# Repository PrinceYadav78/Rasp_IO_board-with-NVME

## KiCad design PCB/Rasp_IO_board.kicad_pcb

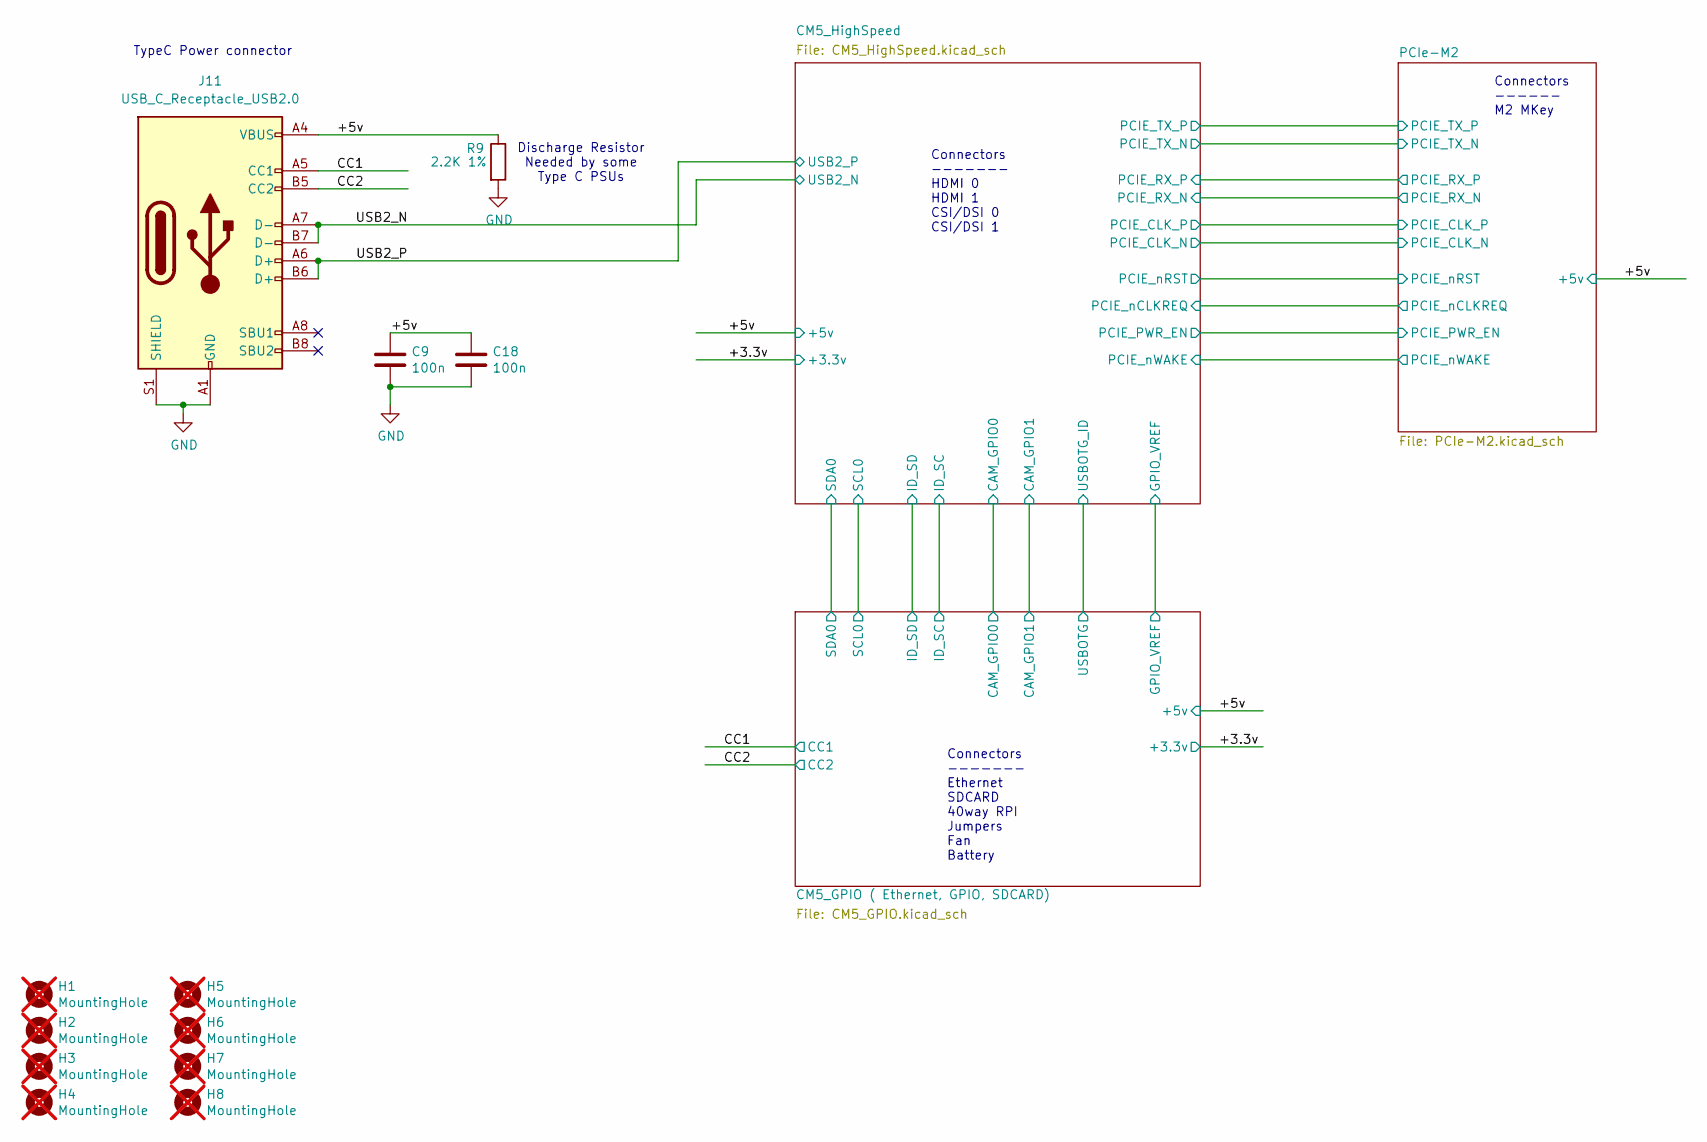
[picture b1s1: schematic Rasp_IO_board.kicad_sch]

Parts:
C9, C18: 100n; C_0402_1005Metric; Part Description 0.1uF 10% 16V Ceramic Capacitor X7R 040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
H1, H2, H3, H4, H5, H6, H7, H8: MountingHole; MountingHole_2.7mm_M2.5_DIN965; Part Description M2.5 mounting hole; not fitted
J11: USB_C_Receptacle_USB2.0; USB_C_Receptacle_GCT_USB4105-xx-A_16P_TopMnt_Horizontal; Part Description USBC USB2 data and power connector
R9: 2.2K 1%; R_0402_1005Metric; Part Description Resistor 2.2K M1005 1% 63mW

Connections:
/+5v: C9.1, C18.1, J11.A4 (VBUS), J11.A9 (VBUS), J11.B4 (VBUS), J11.B9 (VBUS), R9.1; also elsewhere on the board
/CC1: J11.A5 (CC1); also elsewhere on the board
/CC2: J11.B5 (CC2); also elsewhere on the board
/USB2_N: J11.A7 (D-), J11.B7 (D-); also elsewhere on the board
/USB2_P: J11.A6 (D+), J11.B6 (D+); also elsewhere on the board
GND: C9.2, C18.2, J11.A1 (GND), J11.A12 (GND), J11.B1 (GND), J11.B12 (GND), J11.S1 (SHIELD), R9.2; also elsewhere on the board

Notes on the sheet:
Connectors ------- Ethernet SDCARD 40way RPI Jumpers Fan Battery
Connectors ------ M2 MKey
Discharge Resistor Needed by some Type C PSUs
TypeC Power connector
Connectors ------- HDMI 0 HDMI 1 CSI/DSI 0 CSI/DSI 1

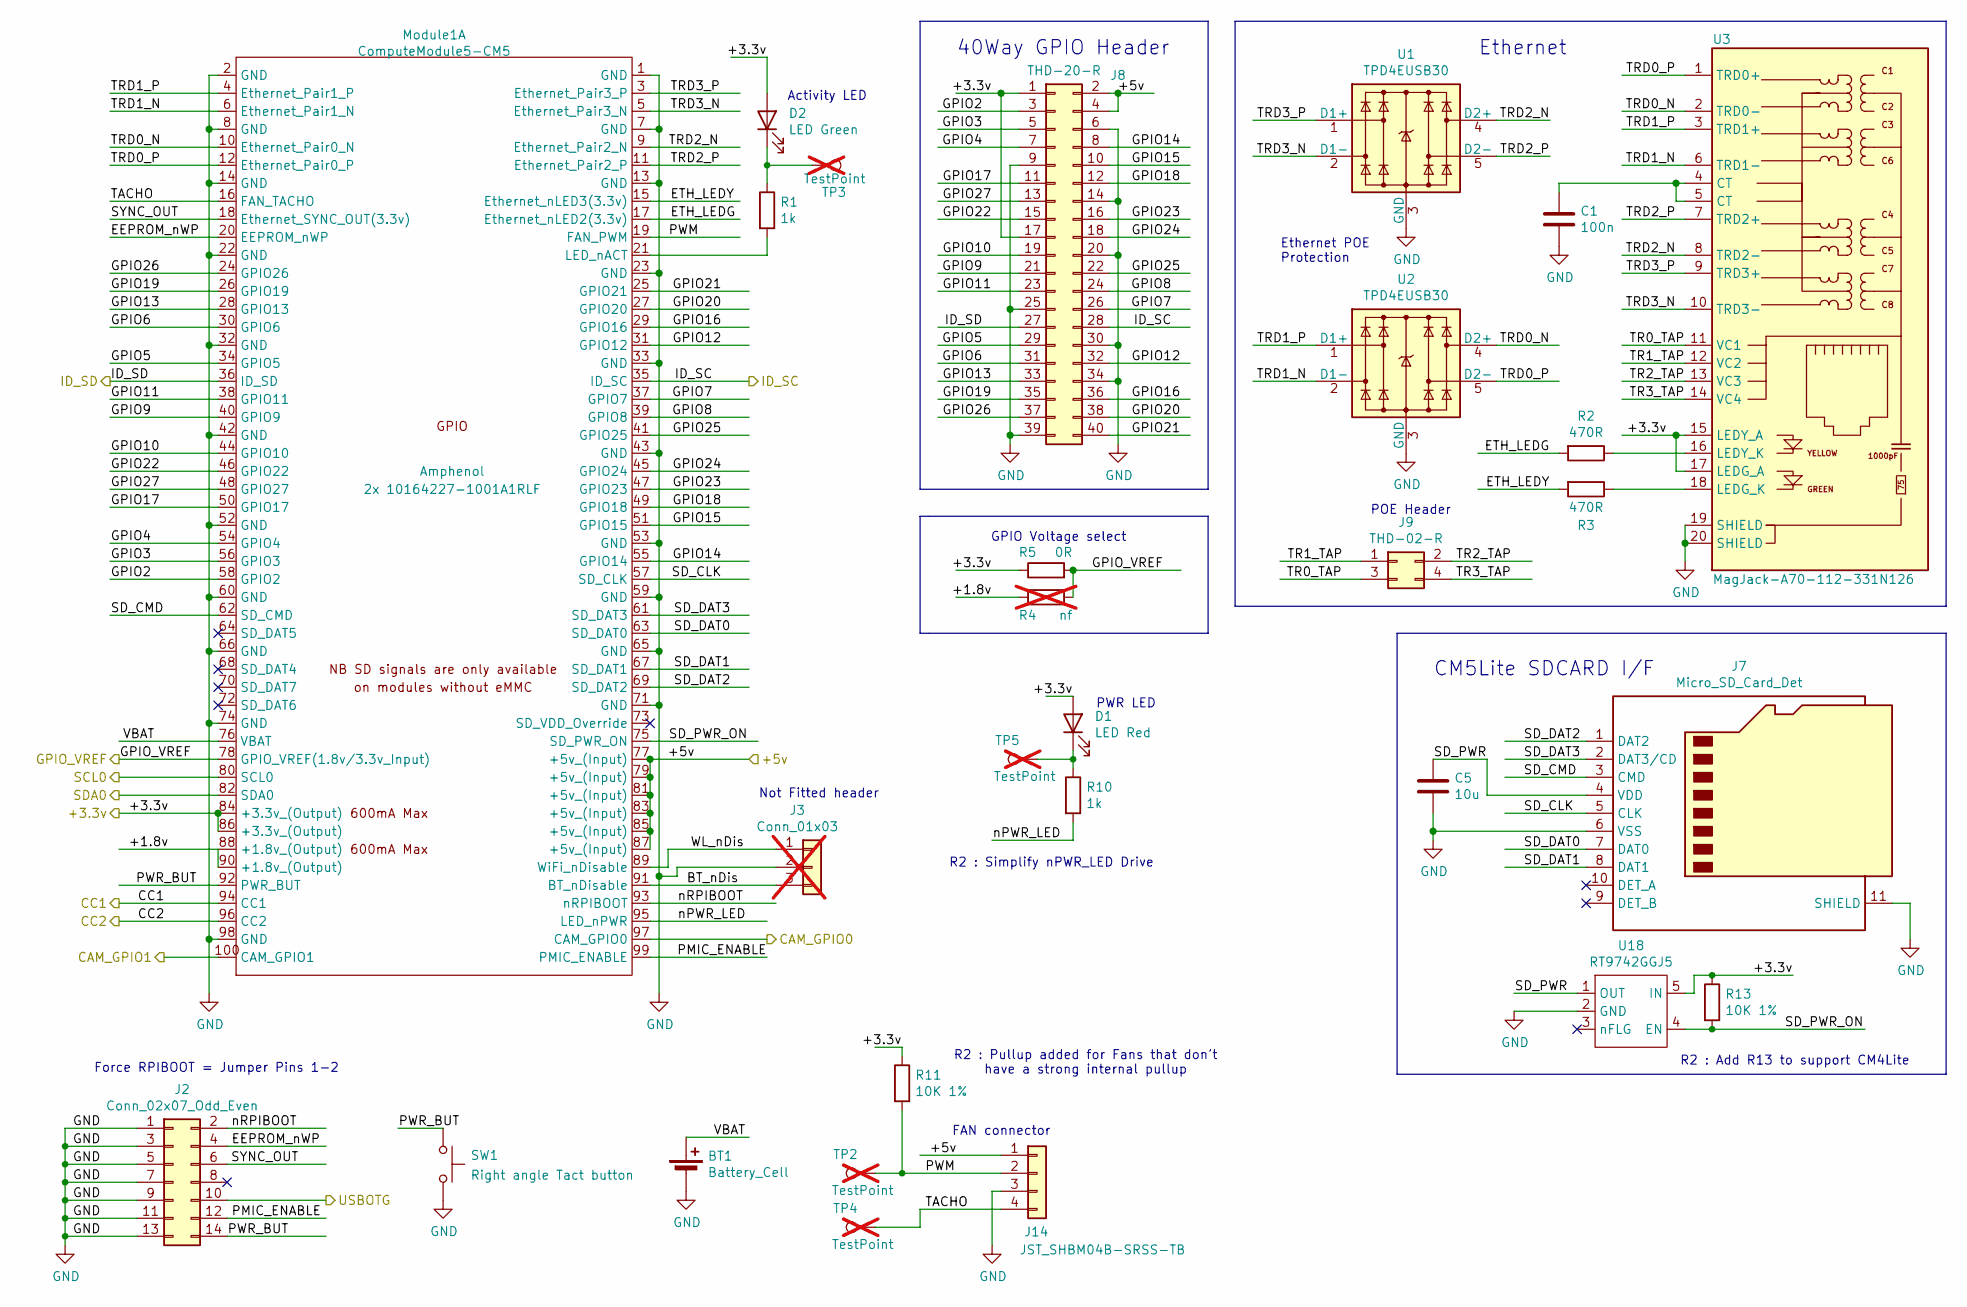
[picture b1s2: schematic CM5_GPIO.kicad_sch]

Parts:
BT1: Battery_Cell; BatteryHolder_Keystone_3034_1x20mm; Part Description Battery Retainer Coin, 20.0mm 1 Cell SM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
C1: 100n; C_0402_1005Metric; Part Description 0.1uF 10% 16V Ceramic Capacitor X7R 040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
C5: 10u; C_0805_2012Metric; Part Description 10uF 10% 10V Ceramic Capacitor X7R 0805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
D1: LED Red; LED_0603_1608Metric; Part Description Red 620nm LED Indication - Discrete 2.2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
D2: LED Green; LED_0603_1608Metric; Part Description Green 572nm LED Indication - Discrete 2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
J2: Conn_02x07_Odd_Even; PinHeader_2x07_P2.54mm_Vertical; Part Description PinHeader_2x07_P2.54mm_Vertical
J3: Conn_01x03; PinHeader_1x03_P2.54mm_Vertical; Part Description 3pin 0.1" connector; not fitted
J7: Micro_SD_Card_Det; SDCARD_MOLEX_503398-1892; Part Description 9 (8 + 1) Position Card Connector micro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
J8: THD-20-R; PinHeader_2x20_P2.54mm_Vertical; Part Description PinHeader_2x20_P2.54mm_Vertical
J9: THD-02-R; PinHeader_2x02_P2.54mm_Vertical; Part Description PinHeader_2x02_P2.54mm_Vertical
J14: JST_SHBM04B-SRSS-TB; JST_SH_BM04B-SRSS-TB_1x04-1MP_P1.00mm_Vertical; Part Description 4 pin vertical 1mm pitch connector
Module1: ComputeModule5-CM5; Raspberry-Pi-5-Compute-Module; Part Description 100 Position Connector Receptacle, Cent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
R1, R10: 1k; R_0402_1005Metric; Part Description Resistor 1K M1005 1% 63mW
R2, R3: 470R; R_0402_1005Metric; Part Description Resistor 470R M1005 1% 63mW
R4: nf; R_0805_2012Metric_Pad1.20x1.40mm_HandSolder; not fitted
R5: 0R; R_0805_2012Metric_Pad1.20x1.40mm_HandSolder; Part Description Resistor 0R M2012 5%
R11, R13: 10K 1%; R_0402_1005Metric; Part Description Resistor 10K M1005 1% 63mW
SW1: Right angle Tact button; SW_Tactile_SPST_Angled_PTS645Vx58-2LFS; Part Description Right angle through hole Tact switch
TP2, TP3, TP4, TP5: TestPoint; TestPoint_Pad_2.0x2.0mm; Part Description Test point; not fitted
U1, U2: TPD4EUSB30; USON-10_2.5x1.0mm_P0.5mm; Part Description Quad TVS diode for high speed signals (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
U3: MagJack-A70-112-331N126; TRJG0926HENL; Part Description Gigabit Ethernet Magjack
U18: RT9742GGJ5; SOT-23-5; Part Description Power Switch/Driver 1:1 N-Channel 1A TS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

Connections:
/+3.3v: D1.2 (A), D2.2 (A), J8.1, J8.17, Module1.84 (+3.3v_(Output)), Module1.86 (+3.3v_(Output)), R5.1, R11.1, R13.1, U3.15 (LEDY_A), U3.17 (LEDG_A), U18.5 (IN); also elsewhere on the board
/+5v: J8.2, J8.4, J14.1, Module1.77 (+5v_(Input)), Module1.79 (+5v_(Input)), Module1.81 (+5v_(Input)), Module1.83 (+5v_(Input)), Module1.85 (+5v_(Input)), Module1.87 (+5v_(Input)); also elsewhere on the board
/CC1: Module1.94 (CC1); also elsewhere on the board
/CC2: Module1.96 (CC2); also elsewhere on the board
/CM5_GPIO ( Ethernet, GPIO, SDCARD)/+1.8v: Module1.88 (+1.8v_(Output)), Module1.90 (+1.8v_(Output)), R4.1
/CM5_GPIO ( Ethernet, GPIO, SDCARD)/BT_nDis: J3.3, Module1.91 (BT_nDisable)
/CM5_GPIO ( Ethernet, GPIO, SDCARD)/CAM_GPIO0: Module1.97 (CAM_GPIO0); also elsewhere on the board
/CM5_GPIO ( Ethernet, GPIO, SDCARD)/CAM_GPIO1: Module1.100 (CAM_GPIO1); also elsewhere on the board
/CM5_GPIO ( Ethernet, GPIO, SDCARD)/EEPROM_nWP: J2.4, Module1.20 (EEPROM_nWP)
/CM5_GPIO ( Ethernet, GPIO, SDCARD)/ETH_LEDG: Module1.17 (Ethernet_nLED2(3.3v)), R2.2
/CM5_GPIO ( Ethernet, GPIO, SDCARD)/ETH_LEDY: Module1.15 (Ethernet_nLED3(3.3v)), R3.2
/CM5_GPIO ( Ethernet, GPIO, SDCARD)/GPIO2: J8.3, Module1.58 (GPIO2)
/CM5_GPIO ( Ethernet, GPIO, SDCARD)/GPIO3: J8.5, Module1.56 (GPIO3)
/CM5_GPIO ( Ethernet, GPIO, SDCARD)/GPIO4: J8.7, Module1.54 (GPIO4)
/CM5_GPIO ( Ethernet, GPIO, SDCARD)/GPIO5: J8.29, Module1.34 (GPIO5)
/CM5_GPIO ( Ethernet, GPIO, SDCARD)/GPIO6: J8.31, Module1.30 (GPIO6)
/CM5_GPIO ( Ethernet, GPIO, SDCARD)/GPIO7: J8.26, Module1.37 (GPIO7)
/CM5_GPIO ( Ethernet, GPIO, SDCARD)/GPIO8: J8.24, Module1.39 (GPIO8)
/CM5_GPIO ( Ethernet, GPIO, SDCARD)/GPIO9: J8.21, Module1.40 (GPIO9)
/CM5_GPIO ( Ethernet, GPIO, SDCARD)/GPIO10: J8.19, Module1.44 (GPIO10)
/CM5_GPIO ( Ethernet, GPIO, SDCARD)/GPIO11: J8.23, Module1.38 (GPIO11)
/CM5_GPIO ( Ethernet, GPIO, SDCARD)/GPIO12: J8.32, Module1.31 (GPIO12)
/CM5_GPIO ( Ethernet, GPIO, SDCARD)/GPIO13: J8.33, Module1.28 (GPIO13)
/CM5_GPIO ( Ethernet, GPIO, SDCARD)/GPIO14: J8.8, Module1.55 (GPIO14)
/CM5_GPIO ( Ethernet, GPIO, SDCARD)/GPIO15: J8.10, Module1.51 (GPIO15)
/CM5_GPIO ( Ethernet, GPIO, SDCARD)/GPIO16: J8.36, Module1.29 (GPIO16)
/CM5_GPIO ( Ethernet, GPIO, SDCARD)/GPIO17: J8.11, Module1.50 (GPIO17)
/CM5_GPIO ( Ethernet, GPIO, SDCARD)/GPIO18: J8.12, Module1.49 (GPIO18)
/CM5_GPIO ( Ethernet, GPIO, SDCARD)/GPIO19: J8.35, Module1.26 (GPIO19)
/CM5_GPIO ( Ethernet, GPIO, SDCARD)/GPIO20: J8.38, Module1.27 (GPIO20)
/CM5_GPIO ( Ethernet, GPIO, SDCARD)/GPIO21: J8.40, Module1.25 (GPIO21)
/CM5_GPIO ( Ethernet, GPIO, SDCARD)/GPIO22: J8.15, Module1.46 (GPIO22)
/CM5_GPIO ( Ethernet, GPIO, SDCARD)/GPIO23: J8.16, Module1.47 (GPIO23)
/CM5_GPIO ( Ethernet, GPIO, SDCARD)/GPIO24: J8.18, Module1.45 (GPIO24)
/CM5_GPIO ( Ethernet, GPIO, SDCARD)/GPIO25: J8.22, Module1.41 (GPIO25)
/CM5_GPIO ( Ethernet, GPIO, SDCARD)/GPIO26: J8.37, Module1.24 (GPIO26)
/CM5_GPIO ( Ethernet, GPIO, SDCARD)/GPIO27: J8.13, Module1.48 (GPIO27)
/CM5_GPIO ( Ethernet, GPIO, SDCARD)/GPIO_VREF: Module1.78 (GPIO_VREF(1.8v/3.3v_Input)), R4.2, R5.2; also elsewhere on the board
/CM5_GPIO ( Ethernet, GPIO, SDCARD)/ID_SC: J8.28, Module1.35 (ID_SC); also elsewhere on the board
/CM5_GPIO ( Ethernet, GPIO, SDCARD)/ID_SD: J8.27, Module1.36 (ID_SD); also elsewhere on the board
/CM5_GPIO ( Ethernet, GPIO, SDCARD)/PMIC_ENABLE: J2.12, Module1.99 (PMIC_ENABLE)
/CM5_GPIO ( Ethernet, GPIO, SDCARD)/PWM: J14.2, Module1.19 (FAN_PWM), R11.2, TP2.1
/CM5_GPIO ( Ethernet, GPIO, SDCARD)/PWR_BUT: J2.14, Module1.92 (PWR_BUT), SW1.1
/CM5_GPIO ( Ethernet, GPIO, SDCARD)/SD_CLK: J7.5 (CLK), Module1.57 (SD_CLK)
/CM5_GPIO ( Ethernet, GPIO, SDCARD)/SD_CMD: J7.3 (CMD), Module1.62 (SD_CMD)
/CM5_GPIO ( Ethernet, GPIO, SDCARD)/SD_DAT0: J7.7 (DAT0), Module1.63 (SD_DAT0)
/CM5_GPIO ( Ethernet, GPIO, SDCARD)/SD_DAT1: J7.8 (DAT1), Module1.67 (SD_DAT1)
/CM5_GPIO ( Ethernet, GPIO, SDCARD)/SD_DAT2: J7.1 (DAT2), Module1.69 (SD_DAT2)
/CM5_GPIO ( Ethernet, GPIO, SDCARD)/SD_DAT3: J7.2 (DAT3/CD), Module1.61 (SD_DAT3)
/CM5_GPIO ( Ethernet, GPIO, SDCARD)/SD_PWR: C5.1, J7.4 (VDD), U18.1 (OUT)
/CM5_GPIO ( Ethernet, GPIO, SDCARD)/SD_PWR_ON: Module1.75 (SD_PWR_ON), R13.2, U18.4 (EN)
/CM5_GPIO ( Ethernet, GPIO, SDCARD)/SYNC_OUT: J2.6, Module1.18 (Ethernet_SYNC_OUT(3.3v))
/CM5_GPIO ( Ethernet, GPIO, SDCARD)/TACHO: J14.4, Module1.16 (FAN_TACHO), TP4.1
/CM5_GPIO ( Ethernet, GPIO, SDCARD)/TR0_TAP: J9.3, U3.11 (VC1)
/CM5_GPIO ( Ethernet, GPIO, SDCARD)/TR1_TAP: J9.1, U3.12 (VC2)
/CM5_GPIO ( Ethernet, GPIO, SDCARD)/TR2_TAP: J9.2, U3.13 (VC3)
/CM5_GPIO ( Ethernet, GPIO, SDCARD)/TR3_TAP: J9.4, U3.14 (VC4)
/CM5_GPIO ( Ethernet, GPIO, SDCARD)/TRD0_N: Module1.10 (Ethernet_Pair0_N), U2.4 (D2+), U2.7, U3.2 (TRD0-)
/CM5_GPIO ( Ethernet, GPIO, SDCARD)/TRD0_P: Module1.12 (Ethernet_Pair0_P), U2.5 (D2-), U2.6, U3.1 (TRD0+)
/CM5_GPIO ( Ethernet, GPIO, SDCARD)/TRD1_N: Module1.6 (Ethernet_Pair1_N), U2.2 (D1-), U2.9, U3.6 (TRD1-)
/CM5_GPIO ( Ethernet, GPIO, SDCARD)/TRD1_P: Module1.4 (Ethernet_Pair1_P), U2.1 (D1+), U2.10, U3.3 (TRD1+)
/CM5_GPIO ( Ethernet, GPIO, SDCARD)/TRD2_N: Module1.9 (Ethernet_Pair2_N), U1.4 (D2+), U1.7, U3.8 (TRD2-)
/CM5_GPIO ( Ethernet, GPIO, SDCARD)/TRD2_P: Module1.11 (Ethernet_Pair2_P), U1.5 (D2-), U1.6, U3.7 (TRD2+)
/CM5_GPIO ( Ethernet, GPIO, SDCARD)/TRD3_N: Module1.5 (Ethernet_Pair3_N), U1.2 (D1-), U1.9, U3.10 (TRD3-)
/CM5_GPIO ( Ethernet, GPIO, SDCARD)/TRD3_P: Module1.3 (Ethernet_Pair3_P), U1.1 (D1+), U1.10, U3.9 (TRD3+)
/CM5_GPIO ( Ethernet, GPIO, SDCARD)/USBOTG: J2.10; also elsewhere on the board
/CM5_GPIO ( Ethernet, GPIO, SDCARD)/VBAT: BT1.1 (+), Module1.76 (VBAT)
/CM5_GPIO ( Ethernet, GPIO, SDCARD)/WL_nDis: J3.1, Module1.89 (WiFi_nDisable)
/CM5_GPIO ( Ethernet, GPIO, SDCARD)/nPWR_LED: Module1.95 (LED_nPWR), R10.2
/CM5_GPIO ( Ethernet, GPIO, SDCARD)/nRPIBOOT: J2.2, Module1.93 (nRPIBOOT)
/CM5_HighSpeed/SCL0: Module1.80 (SCL0); also elsewhere on the board
/CM5_HighSpeed/SDA0: Module1.82 (SDA0); also elsewhere on the board
GND: BT1.2 (-), C1.2, C5.2, J2.1, J2.3, J2.5, J2.7, J2.9, J2.11, J2.13, J3.2, J7.6 (VSS), J7.11 (SHIELD), J8.6, J8.9, J8.14, J8.20, J8.25, J8.30, J8.34, J8.39, J14.3, Module1.1 (GND), Module1.2 (GND), Module1.7 (GND), Module1.8 (GND), Module1.13 (GND), Module1.14 (GND), Module1.22 (GND), Module1.23 (GND), Module1.32 (GND), Module1.33 (GND), Module1.42 (GND), Module1.43 (GND), Module1.52 (GND), Module1.53 (GND), Module1.59 (GND), Module1.60 (GND), Module1.65 (GND), Module1.66 (GND), Module1.71 (GND), Module1.74 (GND), Module1.98 (GND), SW1.2, U1.3 (GND), U1.8 (GND), U2.3 (GND), U2.8 (GND), U3.19 (SHIELD), U3.20 (SHIELD), U18.2 (GND); also elsewhere on the board
unnamed: C1.1, U3.4 (CT), U3.5 (CT)
unnamed: D1.1 (K), R10.1, TP5.1
unnamed: D2.1 (K), R1.1, TP3.1
unnamed: Module1.21 (LED_nACT), R1.2
unnamed: R3.1, U3.18 (LEDG_K)
unnamed: R2.1, U3.16 (LEDY_K)

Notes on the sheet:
40Way GPIO Header
Activity LED
R2 : Simplify nPWR_LED Drive
FAN connector
R2 : Add R13 to support CM4Lite
Ethernet POE Protection
GPIO Voltage select
R2 : Pullup added for Fans that don't have a strong internal pullup
Not Fitted header
POE Header
Force RPIBOOT = Jumper Pins 1-2
PWR LED
Ethernet
CM5Lite SDCARD I/F

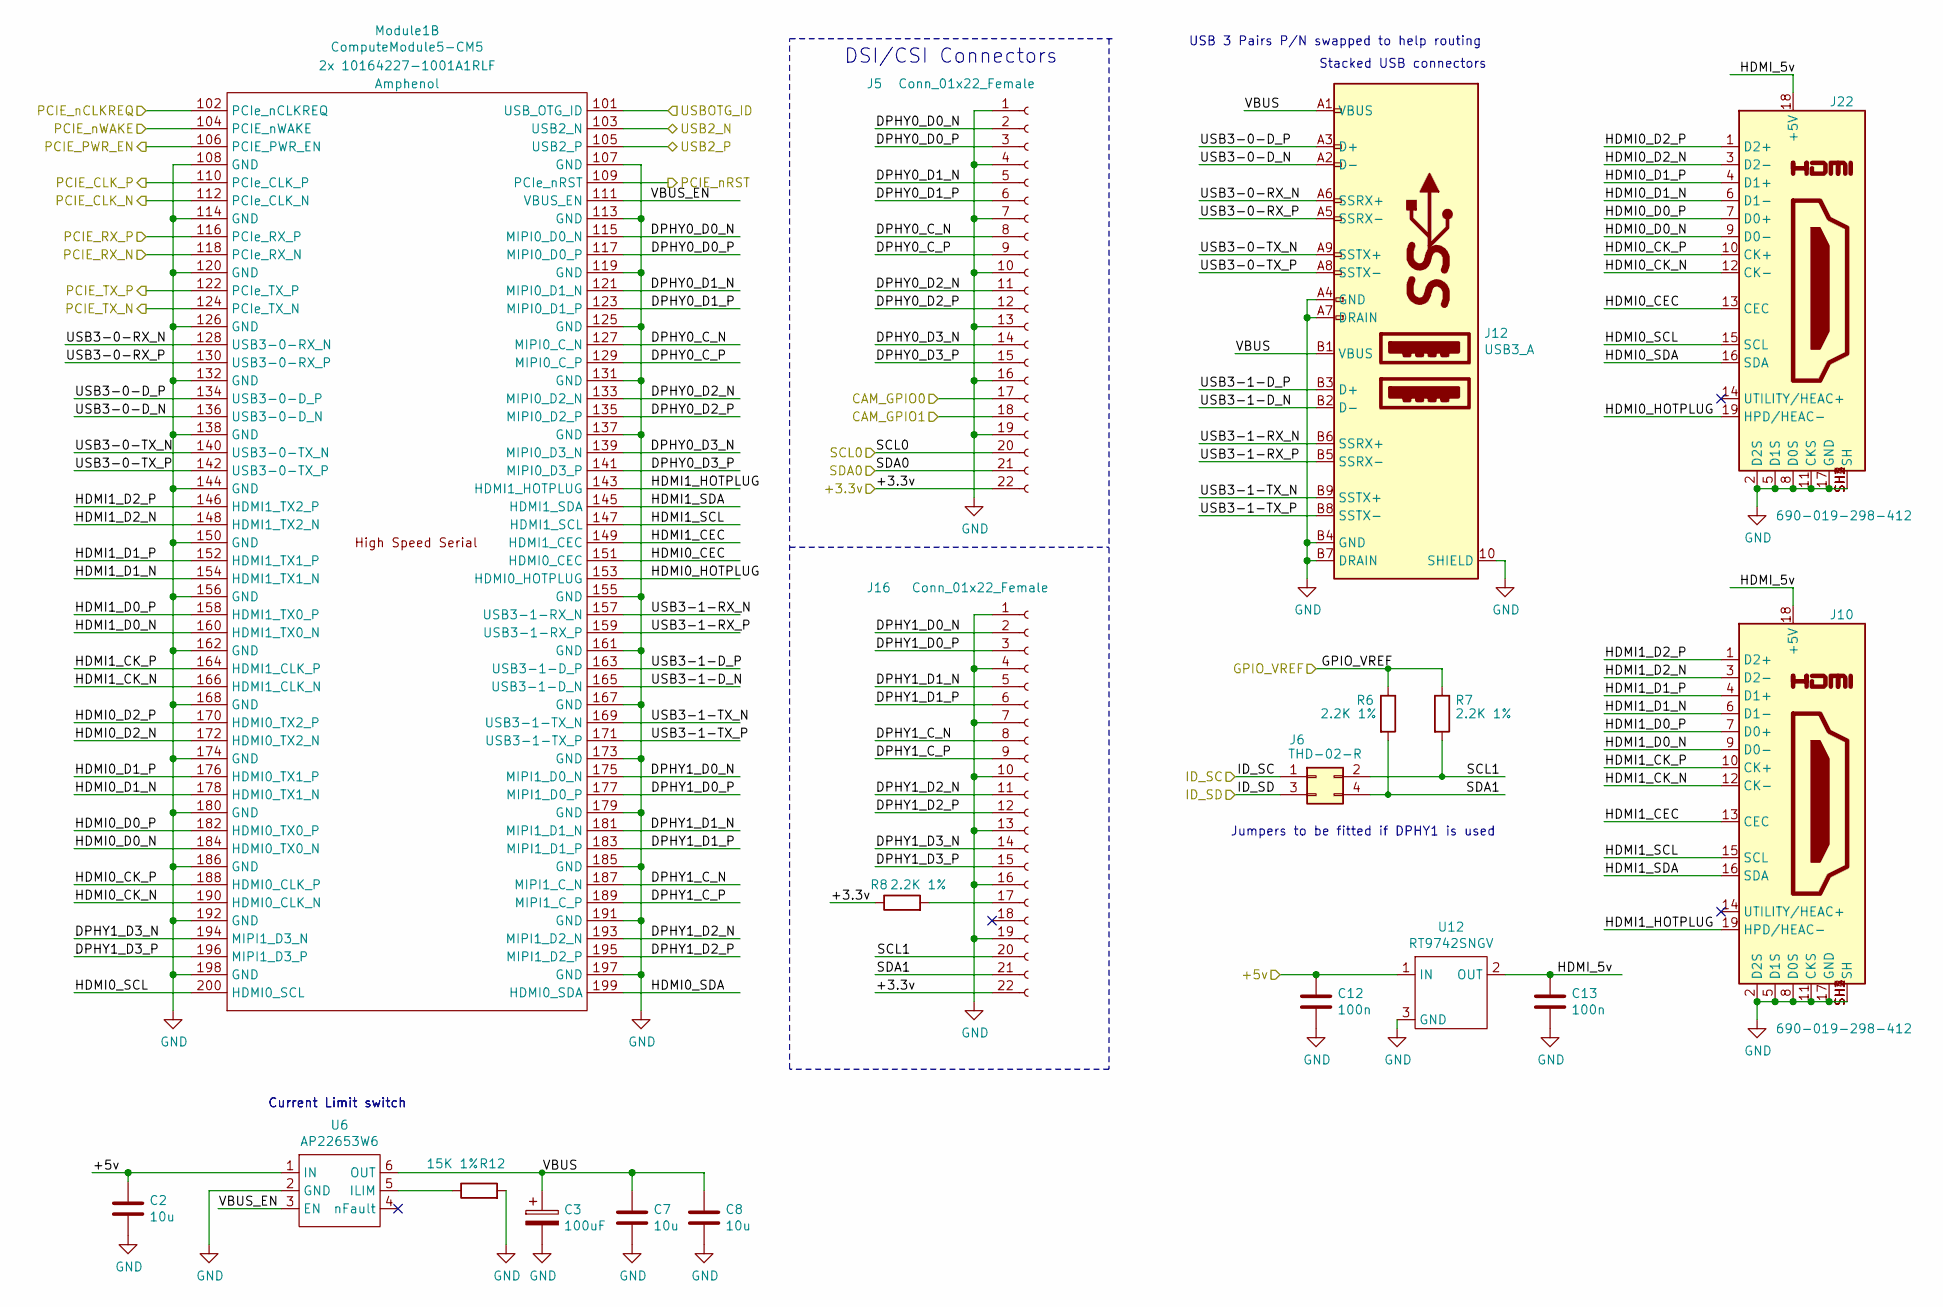
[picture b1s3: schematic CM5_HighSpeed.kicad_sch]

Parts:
C2, C7, C8: 10u; C_0805_2012Metric; Part Description 10uF 10% 10V Ceramic Capacitor X7R 0805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
C3: 100uF; CP_EIA-7343-31_Kemet-D; Part Description Capacitor, SP-Cap, 100u, 6.3V, 15mR ESR
C12, C13: 100n; C_0402_1005Metric; Part Description 0.1uF 10% 16V Ceramic Capacitor X7R 040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
J5, J16: Conn_01x22_Female; Hirose_FH12-22S-0.5SH_1x22-1MP_P0.50mm_Horizontal; Part Description 22 Position FFC, FPC Connector Contacts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
J6: THD-02-R; PinHeader_2x02_P2.54mm_Vertical; Part Description PinHeader_2x02_P2.54mm_Vertical
J10, J22: 690-019-298-412; EDAC 690-019-298-412; Part Description HDMI Connector, Right Angle, 19 Contact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
J12: USB3_A; MTCONN_UBAF30-D2011; Part Description Dual USB 3 connector
Module1: ComputeModule5-CM5; Raspberry-Pi-5-Compute-Module; Part Description 100 Position Connector Receptacle, Cent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
R6, R7, R8: 2.2K 1%; R_0402_1005Metric; Part Description Resistor 2.2K M1005 1% 63mW
R12: 15K 1%; R_0402_1005Metric; Part Description Resistor 15K M1005 1% 63mW
U6: AP22653W6; SOT-23-6; Part Description Power Switch/Driver 1:1 P-Channel 2.1A 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
U12: RT9742SNGV; TSOT-23_HandSoldering; Part Description Power Switch/Driver 1:1 N-Channel 500mA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

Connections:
/+3.3v: J5.22, J16.22, R8.1; also elsewhere on the board
/+5v: C2.1, C12.1, U6.1 (IN), U12.1 (IN); also elsewhere on the board
/CM5_GPIO ( Ethernet, GPIO, SDCARD)/CAM_GPIO0: J5.17; also elsewhere on the board
/CM5_GPIO ( Ethernet, GPIO, SDCARD)/CAM_GPIO1: J5.18; also elsewhere on the board
/CM5_GPIO ( Ethernet, GPIO, SDCARD)/GPIO_VREF: R6.1, R7.1; also elsewhere on the board
/CM5_GPIO ( Ethernet, GPIO, SDCARD)/ID_SC: J6.1; also elsewhere on the board
/CM5_GPIO ( Ethernet, GPIO, SDCARD)/ID_SD: J6.3; also elsewhere on the board
/CM5_GPIO ( Ethernet, GPIO, SDCARD)/USBOTG: Module1.101 (USB_OTG_ID); also elsewhere on the board
/CM5_HighSpeed/DPHY0_C_N: J5.8, Module1.127 (MIPI0_C_N)
/CM5_HighSpeed/DPHY0_C_P: J5.9, Module1.129 (MIPI0_C_P)
/CM5_HighSpeed/DPHY0_D0_N: J5.2, Module1.115 (MIPI0_D0_N)
/CM5_HighSpeed/DPHY0_D0_P: J5.3, Module1.117 (MIPI0_D0_P)
/CM5_HighSpeed/DPHY0_D1_N: J5.5, Module1.121 (MIPI0_D1_N)
/CM5_HighSpeed/DPHY0_D1_P: J5.6, Module1.123 (MIPI0_D1_P)
/CM5_HighSpeed/DPHY0_D2_N: J5.11, Module1.133 (MIPI0_D2_N)
/CM5_HighSpeed/DPHY0_D2_P: J5.12, Module1.135 (MIPI0_D2_P)
/CM5_HighSpeed/DPHY0_D3_N: J5.14, Module1.139 (MIPI0_D3_N)
/CM5_HighSpeed/DPHY0_D3_P: J5.15, Module1.141 (MIPI0_D3_P)
/CM5_HighSpeed/DPHY1_C_N: J16.8, Module1.187 (MIPI1_C_N)
/CM5_HighSpeed/DPHY1_C_P: J16.9, Module1.189 (MIPI1_C_P)
/CM5_HighSpeed/DPHY1_D0_N: J16.2, Module1.175 (MIPI1_D0_N)
/CM5_HighSpeed/DPHY1_D0_P: J16.3, Module1.177 (MIPI1_D0_P)
/CM5_HighSpeed/DPHY1_D1_N: J16.5, Module1.181 (MIPI1_D1_N)
/CM5_HighSpeed/DPHY1_D1_P: J16.6, Module1.183 (MIPI1_D1_P)
/CM5_HighSpeed/DPHY1_D2_N: J16.11, Module1.193 (MIPI1_D2_N)
/CM5_HighSpeed/DPHY1_D2_P: J16.12, Module1.195 (MIPI1_D2_P)
/CM5_HighSpeed/DPHY1_D3_N: J16.14, Module1.194 (MIPI1_D3_N)
/CM5_HighSpeed/DPHY1_D3_P: J16.15, Module1.196 (MIPI1_D3_P)
/CM5_HighSpeed/HDMI0_CEC: J22.13 (CEC), Module1.151 (HDMI0_CEC)
/CM5_HighSpeed/HDMI0_CK_N: J22.12 (CK-), Module1.190 (HDMI0_CLK_N)
/CM5_HighSpeed/HDMI0_CK_P: J22.10 (CK+), Module1.188 (HDMI0_CLK_P)
/CM5_HighSpeed/HDMI0_D0_N: J22.9 (D0-), Module1.184 (HDMI0_TX0_N)
/CM5_HighSpeed/HDMI0_D0_P: J22.7 (D0+), Module1.182 (HDMI0_TX0_P)
/CM5_HighSpeed/HDMI0_D1_N: J22.6 (D1-), Module1.178 (HDMI0_TX1_N)
/CM5_HighSpeed/HDMI0_D1_P: J22.4 (D1+), Module1.176 (HDMI0_TX1_P)
/CM5_HighSpeed/HDMI0_D2_N: J22.3 (D2-), Module1.172 (HDMI0_TX2_N)
/CM5_HighSpeed/HDMI0_D2_P: J22.1 (D2+), Module1.170 (HDMI0_TX2_P)
/CM5_HighSpeed/HDMI0_HOTPLUG: J22.19 (HPD/HEAC-), Module1.153 (HDMI0_HOTPLUG)
/CM5_HighSpeed/HDMI0_SCL: J22.15 (SCL), Module1.200 (HDMI0_SCL)
/CM5_HighSpeed/HDMI0_SDA: J22.16 (SDA), Module1.199 (HDMI0_SDA)
/CM5_HighSpeed/HDMI1_CEC: J10.13 (CEC), Module1.149 (HDMI1_CEC)
/CM5_HighSpeed/HDMI1_CK_N: J10.12 (CK-), Module1.166 (HDMI1_CLK_N)
/CM5_HighSpeed/HDMI1_CK_P: J10.10 (CK+), Module1.164 (HDMI1_CLK_P)
/CM5_HighSpeed/HDMI1_D0_N: J10.9 (D0-), Module1.160 (HDMI1_TX0_N)
/CM5_HighSpeed/HDMI1_D0_P: J10.7 (D0+), Module1.158 (HDMI1_TX0_P)
/CM5_HighSpeed/HDMI1_D1_N: J10.6 (D1-), Module1.154 (HDMI1_TX1_N)
/CM5_HighSpeed/HDMI1_D1_P: J10.4 (D1+), Module1.152 (HDMI1_TX1_P)
/CM5_HighSpeed/HDMI1_D2_N: J10.3 (D2-), Module1.148 (HDMI1_TX2_N)
/CM5_HighSpeed/HDMI1_D2_P: J10.1 (D2+), Module1.146 (HDMI1_TX2_P)
/CM5_HighSpeed/HDMI1_HOTPLUG: J10.19 (HPD/HEAC-), Module1.143 (HDMI1_HOTPLUG)
/CM5_HighSpeed/HDMI1_SCL: J10.15 (SCL), Module1.147 (HDMI1_SCL)
/CM5_HighSpeed/HDMI1_SDA: J10.16 (SDA), Module1.145 (HDMI1_SDA)
/CM5_HighSpeed/HDMI_5v: C13.1, J10.18 (+5V), J22.18 (+5V), U12.2 (OUT)
/CM5_HighSpeed/PCIE_CLK_N: Module1.112 (PCIe_CLK_N); also elsewhere on the board
/CM5_HighSpeed/PCIE_CLK_P: Module1.110 (PCIe_CLK_P); also elsewhere on the board
/CM5_HighSpeed/PCIE_PWR_EN: Module1.106 (PCIE_PWR_EN); also elsewhere on the board
/CM5_HighSpeed/PCIE_RX_N: Module1.118 (PCIe_RX_N); also elsewhere on the board
/CM5_HighSpeed/PCIE_RX_P: Module1.116 (PCIe_RX_P); also elsewhere on the board
/CM5_HighSpeed/PCIE_TX_N: Module1.124 (PCIe_TX_N); also elsewhere on the board
/CM5_HighSpeed/PCIE_TX_P: Module1.122 (PCIe_TX_P); also elsewhere on the board
/CM5_HighSpeed/PCIE_nCLKREQ: Module1.102 (PCIe_nCLKREQ); also elsewhere on the board
/CM5_HighSpeed/PCIE_nRST: Module1.109 (PCIe_nRST); also elsewhere on the board
/CM5_HighSpeed/PCIE_nWAKE: Module1.104 (PCIE_nWAKE); also elsewhere on the board
/CM5_HighSpeed/SCL0: J5.20; also elsewhere on the board
/CM5_HighSpeed/SCL1: J6.2, J16.20, R7.2
/CM5_HighSpeed/SDA0: J5.21; also elsewhere on the board
/CM5_HighSpeed/SDA1: J6.4, J16.21, R6.2
/CM5_HighSpeed/USB3-0-D_N: J12.A2 (D-), Module1.136 (USB3-0-D_N)
/CM5_HighSpeed/USB3-0-D_P: J12.A3 (D+), Module1.134 (USB3-0-D_P)
/CM5_HighSpeed/USB3-0-RX_N: J12.A6 (SSRX+), Module1.128 (USB3-0-RX_N)
/CM5_HighSpeed/USB3-0-RX_P: J12.A5 (SSRX-), Module1.130 (USB3-0-RX_P)
/CM5_HighSpeed/USB3-0-TX_N: J12.A9 (SSTX+), Module1.140 (USB3-0-TX_N)
/CM5_HighSpeed/USB3-0-TX_P: J12.A8 (SSTX-), Module1.142 (USB3-0-TX_P)
/CM5_HighSpeed/USB3-1-D_N: J12.B2 (D-), Module1.165 (USB3-1-D_N)
/CM5_HighSpeed/USB3-1-D_P: J12.B3 (D+), Module1.163 (USB3-1-D_P)
/CM5_HighSpeed/USB3-1-RX_N: J12.B6 (SSRX+), Module1.157 (USB3-1-RX_N)
/CM5_HighSpeed/USB3-1-RX_P: J12.B5 (SSRX-), Module1.159 (USB3-1-RX_P)
/CM5_HighSpeed/USB3-1-TX_N: J12.B9 (SSTX+), Module1.169 (USB3-1-TX_N)
/CM5_HighSpeed/USB3-1-TX_P: J12.B8 (SSTX-), Module1.171 (USB3-1-TX_P)
/CM5_HighSpeed/VBUS: C3.1, C7.1, C8.1, J12.A1 (VBUS), J12.B1 (VBUS), U6.6 (OUT)
/CM5_HighSpeed/VBUS_EN: Module1.111 (VBUS_EN), U6.3 (EN)
/USB2_N: Module1.103 (USB2_N); also elsewhere on the board
/USB2_P: Module1.105 (USB2_P); also elsewhere on the board
GND: C2.2, C3.2, C7.2, C8.2, C12.2, C13.2, J5.1, J5.4, J5.7, J5.10, J5.13, J5.16, J5.19, J10.2 (D2S), J10.5 (D1S), J10.8 (D0S), J10.11 (CKS), J10.17 (GND), J10.SH1 (SH), J10.SH2 (SH), J10.SH3 (SH), J10.SH4 (SH), J12.10 (SHIELD), J12.A4 (GND), J12.A7 (DRAIN), J12.B4 (GND), J12.B7 (DRAIN), J16.1, J16.4, J16.7, J16.10, J16.13, J16.16, J16.19, J22.2 (D2S), J22.5 (D1S), J22.8 (D0S), J22.11 (CKS), J22.17 (GND), J22.SH1 (SH), J22.SH2 (SH), J22.SH3 (SH), J22.SH4 (SH), Module1.107 (GND), Module1.108 (GND), Module1.113 (GND), Module1.114 (GND), Module1.119 (GND), Module1.120 (GND), Module1.125 (GND), Module1.126 (GND), Module1.131 (GND), Module1.132 (GND), Module1.137 (GND), Module1.138 (GND), Module1.144 (GND), Module1.150 (GND), Module1.155 (GND), Module1.156 (GND), Module1.161 (GND), Module1.162 (GND), Module1.167 (GND), Module1.168 (GND), Module1.173 (GND), Module1.174 (GND), Module1.179 (GND), Module1.180 (GND), Module1.185 (GND), Module1.186 (GND), Module1.191 (GND), Module1.192 (GND), Module1.197 (GND), Module1.198 (GND), R12.2, U6.2 (GND), U12.3 (GND); also elsewhere on the board
unnamed: J16.17, R8.2
unnamed: R12.1, U6.5 (ILIM)

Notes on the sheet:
USB 3 Pairs P/N swapped to help routing
Jumpers to be fitted if DPHY1 is used
Current Limit switch
DSI/CSI Connectors
Stacked USB connectors

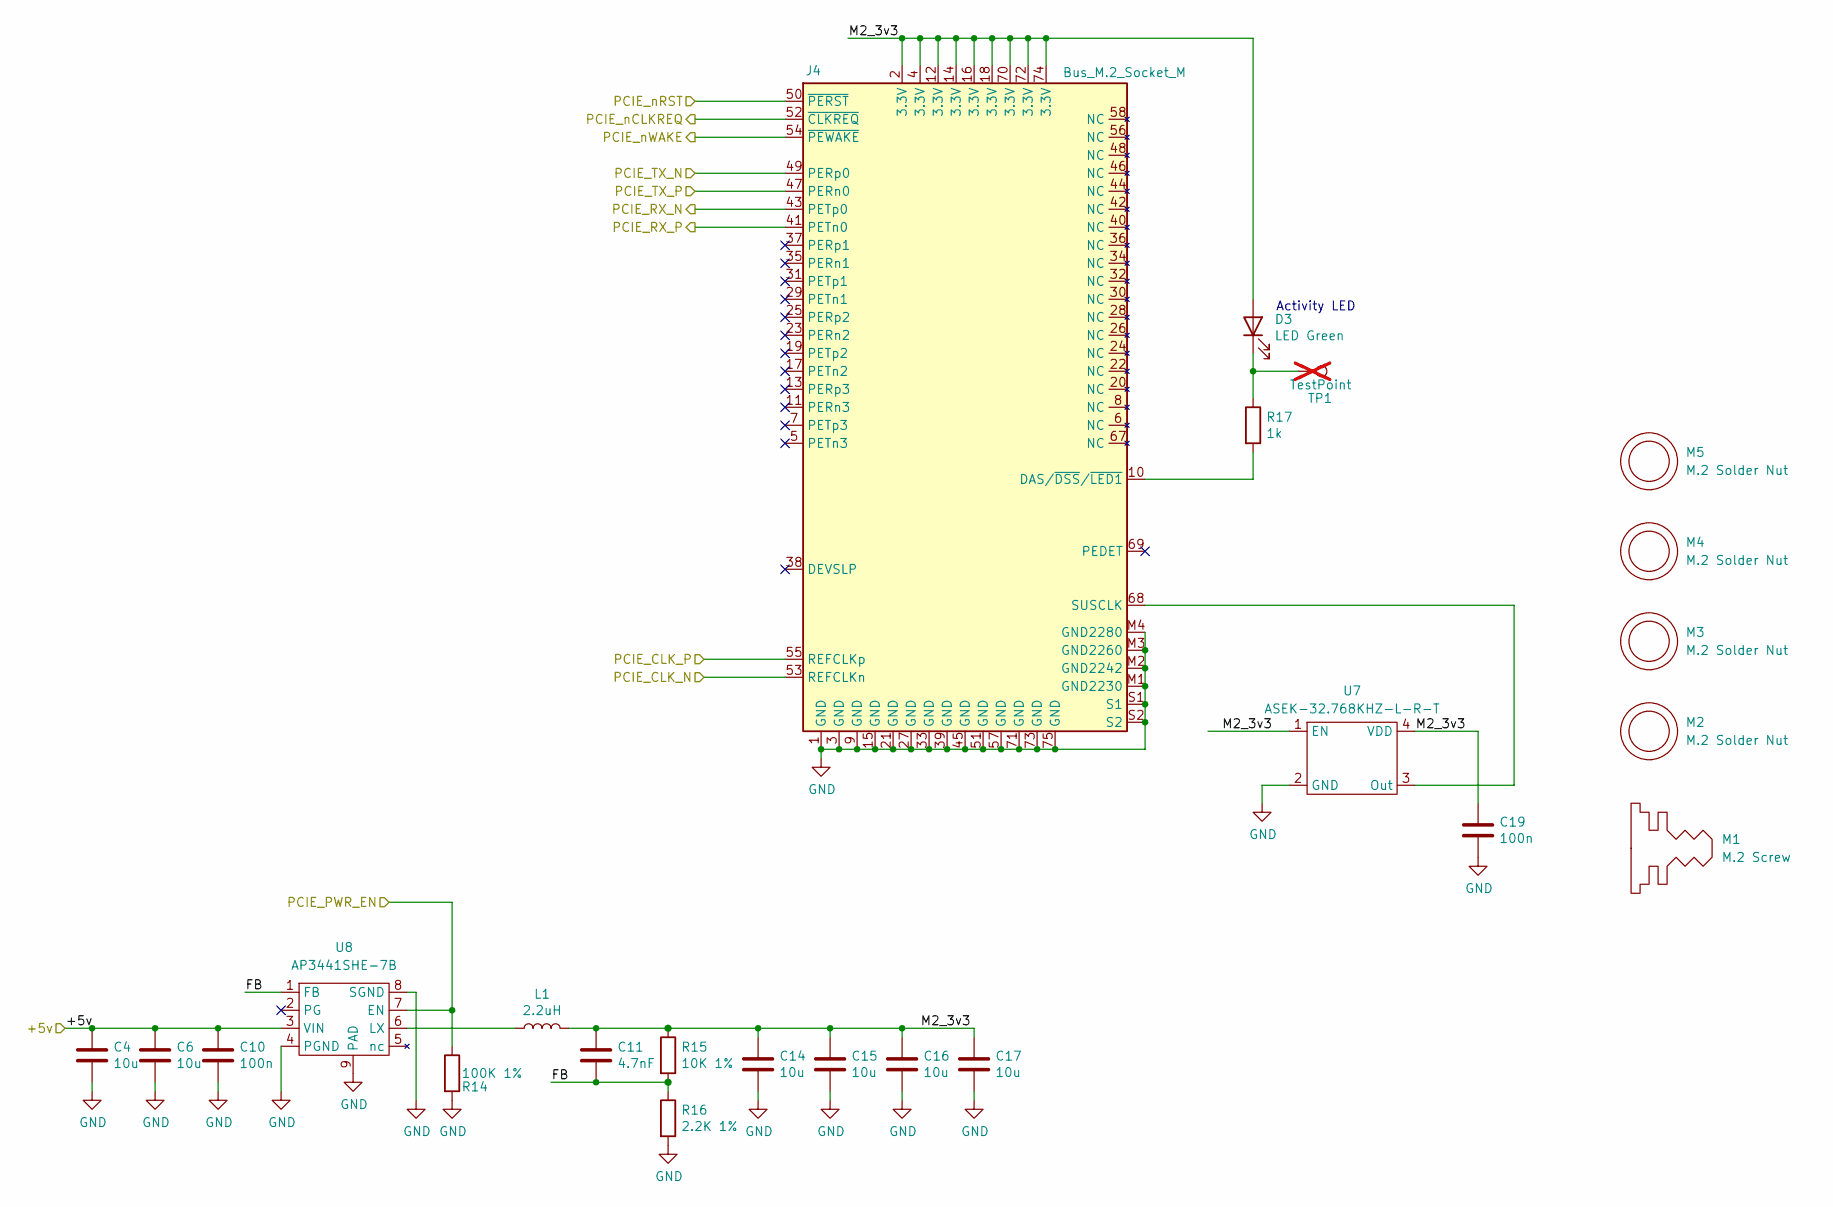
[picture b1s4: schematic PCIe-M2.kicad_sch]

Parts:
C4, C6, C14, C15, C16, C17: 10u; C_0805_2012Metric; Part Description 10uF 10% 10V Ceramic Capacitor X7R 0805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
C10, C19: 100n; C_0402_1005Metric; Part Description 0.1uF 10% 16V Ceramic Capacitor X7R 040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
C11: 4.7nF; C_0402_1005Metric; Part Description 4.7nF capacitor 0402
D3: LED Green; LED_0603_1608Metric; Part Description Green 572nm LED Indication - Discrete 2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
J4: Bus_M.2_Socket_M; M.2 M Key socket; Part Description M.2 M Key connector
L1: 2.2uH; L_Bourns_SRP5030CC; Part Description Inductor, SMT, 2520, 2u2, IRMS=7A, ISAT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
M1: M.2 Screw; Part Description M.2 Screw
M2, M3, M4, M5: M.2 Solder Nut; Part Description Solder nut for M.2 slot
R14: 100K 1%; R_0402_1005Metric; Part Description Resistor 100K M1005 1% 63mW
R15: 10K 1%; R_0402_1005Metric; Part Description Resistor 10K M1005 1% 63mW
R16: 2.2K 1%; R_0402_1005Metric; Part Description Resistor 2.2K M1005 1% 63mW
R17: 1k; R_0402_1005Metric; Part Description Resistor 1K M1005 1% 63mW
TP1: TestPoint; TestPoint_Pad_2.0x2.0mm; Part Description Test point; not fitted
U7: ASEK-32.768KHZ-L-R-T; Crystal_SMD_3225-4Pin_3.2x2.5mm; Part Description 32KHz Xtal oscilator
U8: AP3441SHE-7B; DFN-8-1EP_2x2mm_P0.5mm_EP1.05x1.75mm; Part Description 3A DC-DC converter

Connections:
/+5v: C4.1, C6.1, C10.1, U8.3 (VIN); also elsewhere on the board
/CM5_HighSpeed/PCIE_CLK_N: J4.53 (REFCLKn); also elsewhere on the board
/CM5_HighSpeed/PCIE_CLK_P: J4.55 (REFCLKp); also elsewhere on the board
/CM5_HighSpeed/PCIE_PWR_EN: R14.1, U8.7 (EN); also elsewhere on the board
/CM5_HighSpeed/PCIE_RX_N: J4.43 (PETp0); also elsewhere on the board
/CM5_HighSpeed/PCIE_RX_P: J4.41 (PETn0); also elsewhere on the board
/CM5_HighSpeed/PCIE_TX_N: J4.49 (PERp0); also elsewhere on the board
/CM5_HighSpeed/PCIE_TX_P: J4.47 (PERn0); also elsewhere on the board
/CM5_HighSpeed/PCIE_nCLKREQ: J4.52 (~CLKREQ); also elsewhere on the board
/CM5_HighSpeed/PCIE_nRST: J4.50 (~PERST); also elsewhere on the board
/CM5_HighSpeed/PCIE_nWAKE: J4.54 (~PEWAKE); also elsewhere on the board
/PCIe-M2/FB: C11.2, R15.2, R16.1, U8.1 (FB)
/PCIe-M2/M2_3v3: C11.1, C14.1, C15.1, C16.1, C17.1, C19.1, D3.2 (A), J4.2 (3.3V), J4.4 (3.3V), J4.12 (3.3V), J4.14 (3.3V), J4.16 (3.3V), J4.18 (3.3V), J4.70 (3.3V), J4.72 (3.3V), J4.74 (3.3V), L1.2, R15.1, U7.1 (EN), U7.4 (VDD)
GND: C4.2, C6.2, C10.2, C14.2, C15.2, C16.2, C17.2, C19.2, J4.1 (GND), J4.3 (GND), J4.9 (GND), J4.15 (GND), J4.21 (GND), J4.27 (GND), J4.33 (GND), J4.39 (GND), J4.45 (GND), J4.51 (GND), J4.57 (GND), J4.71 (GND), J4.73 (GND), J4.75 (GND), J4.M1 (GND2230), J4.M2 (GND2242), J4.M3 (GND2260), J4.M4 (GND2280), J4.S1, J4.S2, R14.2, R16.2, U7.2 (GND), U8.4 (PGND), U8.8 (SGND), U8.9 (PAD); also elsewhere on the board
unnamed: D3.1 (K), R17.1, TP1.1
unnamed: J4.10 (DAS/~DSS/~LED1), R17.2
unnamed: J4.68 (SUSCLK), U7.3 (Out)
unnamed: L1.1, U8.6 (LX)

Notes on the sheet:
Activity LED
